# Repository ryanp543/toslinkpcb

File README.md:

# TOSLink Transceiver (Tool and Control Box)

## Overview

This repository contains the Autodesk Eagle schematic and layout for the TOSLink transceivers on the control box and the tools used by the MIT Bioinstrumentation Lab rover. 

For sending and receiving data to and from the tools over the TOSLink optic fiber cables, the TTL interface on a TinkerForge RS232 bricklet was used to communicate with an off-the-shelf TOSLink transceiver. This transceiver and the required external components were mounted on a custom PCB that easily meshed with the TTL breakout pins without needing any external wires and matched the RS232 bricklet footprint. In other words, this PCB could be mounted on top of the RS232 bricklet with only a couple of screws and male-female 12 mm long standoffs. The RS232 bricklet sends and receives data over the TTL/TOSLink interface at a serial baudrate of 115200 Baud.

The same TOSLink transceiver in the control box is mounted on a custom-made PCB board for the universal tool interface. It receives commands from the control box and returns data to be analyzed. The associated signal communication protocol is UART/USART/TTL, so the four output pins on the PCB correspond to power, ground, transmitter (TX), and receiver (RX). These pins can be accessed with most available four-pin connector housings. 

The `TOSLink Tool V2` and `TOSLink Transceiver V3` directories contain the layout and schematics for the transceiver mounted to the tool interface and the control box RS232 bricklet, respectively. 

## Contributors

#### Primary Contributors
Ryan Poon from the [MIT Bioinstrumentation Lab](https://bioinstrumentation.mit.edu/) is the primary contributor of this project.

#### Other Contributors
Professor Ian Hunter served as the main advisor.

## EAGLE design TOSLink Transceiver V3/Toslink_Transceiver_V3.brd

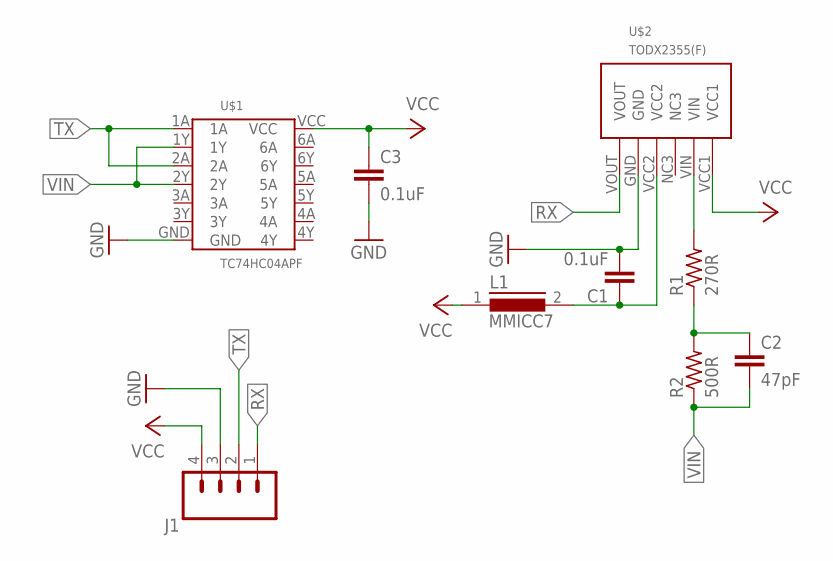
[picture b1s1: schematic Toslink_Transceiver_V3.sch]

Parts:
C1, C3: 0.1uF; C2.5-2
C2: 47pF; C2.5-2
J1: CONN_04; 1X04
L1: MMICC7
R1: 270R; 0204/5
R2: 500R; 0204/5
U$1: TC74HC04APF; DIP14-P-300-2.54
U$2: TODX2355(F)

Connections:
GND: C1.2, C3.2, J1.3, U$1.GND, U$2.GND
unnamed: C1.1, L1.2, U$2.VCC2
unnamed: R1.2, U$2.VIN
unnamed: C2.1, R1.1, R2.2
RX: J1.1, U$2.VOUT
TX: J1.2, U$1.1A, U$1.2A
VCC: C3.1, J1.4, L1.1, U$1.VCC, U$2.VCC1
VIN: C2.2, R2.1, U$1.1Y, U$1.2Y

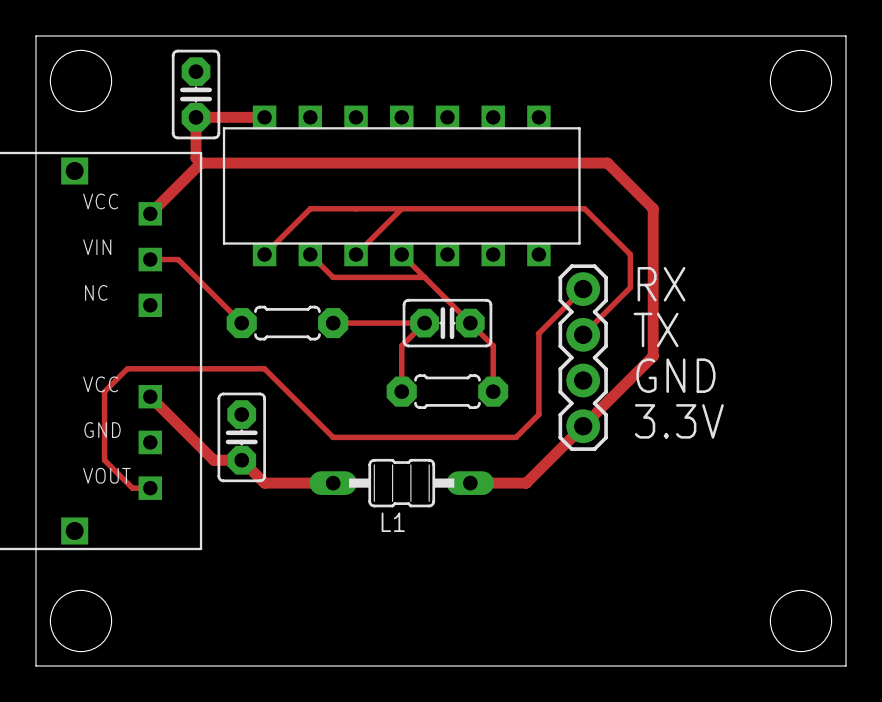
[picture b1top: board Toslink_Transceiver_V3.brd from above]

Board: 2 copper layers, 45.0 x 35.0 mm, 9 parts (0 on the bottom side), 8 nets.

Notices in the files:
parts and their libraries:
SparkFun-Connectors: Licensing: Creative Commons ShareAlike 4.0 International - https://creativecommons.org/licenses/by-sa/4.0
